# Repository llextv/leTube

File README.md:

# LeTube

**10 addressable LED tubes for stage lighting, controlled with Art-Net and QLC+.**

LeTube is a DIY project to build a set of 10 LED tubes for stage lighting.

The goal is pretty simple: build something similar to commercial pixel tubes, but for much less money and using hardware that I can actually modify and repair myself.

The tubes use WS2815 12V LED strips and are controlled by a single ESP32 running WLED. QLC+ sends the lighting data through Art-Net over Wi-Fi.

---

# Why am I doing this?

Commercial pixel tubes can get expensive very quickly when you need 10 of them.

I wanted to build my own version instead of buying ready-made tubes.

Another choice I made was to **not put an ESP32 inside every tube**. All the tubes are controlled from one ESP32, which keeps the electronics inside the tubes very simple.

The current version is mainly a prototype / personal project. I'm not trying to make a commercial product with it.

---

# Overview

## Features

* 10 × 1 m LED tubes
* WS2815 12V addressable RGB LEDs
* 144 LEDs/m
* One ESP32 for all 10 tubes
* Art-Net over Wi-Fi
* QLC+ compatible
* WLED based
* Centralized 12V power supply
* Power distribution using busbars
* Aluminium profiles with diffusers
* No controller inside the tubes

---

# Pictures

## 3D / Assembly

## WLED

---

# How it works
QLC+ generates the DMX values and sends them to the ESP32 using Art-Net.

The ESP32 receives the data and WLED handles the LED output.

Each tube contains a 1 meter section of WS2815 strip, so every LED can be controlled individually.

---

# LED Tubes

Each tube is made from an aluminium LED profile with a diffuser.

The current design uses:

* 1 m aluminium profile
* 1 m WS2815 strip
* 12V power
* LED diffuser
* Wiring for power and data

There is no microcontroller inside the tube.

The 10 tubes are connected back to the central controller and power distribution.

---

# Power

The whole LED system is powered from a **12V 600W power supply**.

I use two busbars to distribute the power.

The ESP32 is powered separately.

The reason for using centralized power is mostly simplicity. I don't need a power supply or converter inside every tube.

**The power supply can deliver a lot of current, so the final installation needs properly sized wiring and suitable protection/fusing.**

---

# Control

## WLED

The ESP32 runs WLED.

WLED is used to handle the addressable LEDs and the network communication.

Official documentation:

https://kno.wled.ge/

---

# Hardware

Main components:

* ESP32
* WS2815 12V LED strip
* Aluminium LED profiles
* LED diffusers
* 12V 600W power supply
* M6 power busbars
* Wiring and connectors

The complete BOM is available here:

[BOM.csv](BOM.csv)

---

# Project Files

## KiCad

The KiCad files are available here:

* [PCB](assets/tube.kicad_pcb)
* [Project](assets/tube.kicad_pro)
* [Schematic](assets/tube.kicad_sch)

## CAD

* [STEP model](cad/LeTube.step)

Usage of LeTube.step: this component is used for maintain the tube in horizontal position
---

# BOM

| Category           | Item                                        | Quantity | Unit Price (€) |    Total (€) | Notes                   |
| ------------------ | ------------------------------------------- | -------: | -------------: | -----------: | ----------------------- |
| Power Supply       | 12 V 600 W Switching Power Supply           |        1 |          35.99 |        35.99 | Main power supply       |
| Power Distribution | M6 Battery Bus Bar Power Distribution Block |        2 |           6.50 |        13.00 | 1 positive + 1 negative |
| LED Profile        | Aluminium LED Profile, 0.5 m                |       20 |           2.55 |        51.00 | 10 m total              |
| LED Strip          | WS2815 Addressable RGB LED Strip            |     10 m |          6.656 |        66.56 | 12 V                    |
| Wiring             | Electrical Wire                             |        — |           0.00 |         0.00 | Already available       |
| Controller         | ESP-WROOM-32                                |        1 |           0.00 |         0.00 | Already available       |
| **TOTAL**          |                                             |          |                | **176.55 €** | ≈ **195 USD**           |

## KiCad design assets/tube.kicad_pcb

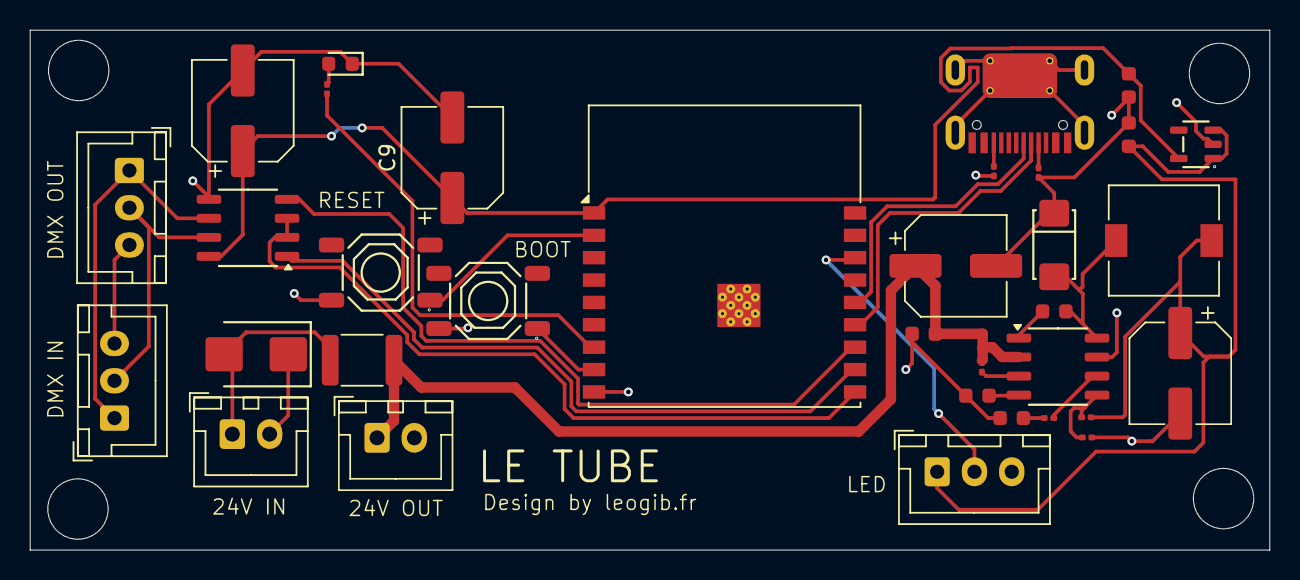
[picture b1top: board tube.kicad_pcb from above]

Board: 2 copper layers, 83.1 x 34.9 mm, 34 parts (0 on the bottom side), 26 nets.

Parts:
C1: 100 nF; C_0603
C2: 220 µF; CP_Elec_6.3x7.7
C3, C6, C9: 100 µF; CP_Elec_6.3x5.8
C4, C5: 10 nF; C_0603
C7, C8: 1uF; C_0603
C10: 100nF; C_0603
D1: SS34; D_DO-214AC(SMA)
D2: SMBJ33A; D_SMB
D3: LED; D_0603
F1: MF-MSMF200; Fuse_1812_4532Metric
J1: LED; JST_XH_B3B-XH-A_1x03_P2.50mm_Vertical
J2: 24V OUT; JST_XH_B2B-XH-A_1x02_P2.50mm_Vertical
J3: 24V IN; JST_XH_B2B-XH-A_1x02_P2.50mm_Vertical
J5: DMX OUT; JST_XH_B3B-XH-A_1x03_P2.50mm_Vertical
J6: USB_C_Receptacle_USB2.0_14P; TYPE-C-SMD_HX-TYPE-C-16PIN
J7: DMX IN; JST_XH_B3B-XH-A_1x03_P2.50mm_Vertical
L1: 22 µH 4 A; L_7.3x7.3_H4.5
R1: R100k; C_0201_0603Metric
R2, R4: R5.1k; C_0201_0603Metric
R3: R330; C_0201_0603Metric
R5: R105k; C_0201_0603Metric
R6: R20k; C_0201_0603Metric
R7: R10k; C_0201_0603Metric
SW2: RESET; SW-SMD_4P-L5.1-W5.1-P3.70-LS6.5-TL-2
SW3: Boot; SW-SMD_4P-L5.1-W5.1-P3.70-LS6.5-TL-2
U1: ESP32-C3-WROOM-02
U2: MAX3485; SOIC-8_3.9x4.9mm_P1.27mm
U3: TPS54331DR; SOIC-8_3.9x4.9mm_P1.27mm
U4: AP2112K-3.3; SOT-23-5_L3.0-W1.7-P0.95-LS2.8-BL

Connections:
3.3V: C6.1, C8.2, C9.1, U1.1 (3V3), U2.8 (VCC), U4.5 (VOUT)
+5V: C3.1, C7.1, J1.1, L1.2, R5.2, U4.1 (VIN), U4.3 (EN)
+24V: C2.1, C10.2, F1.1, J2.1, R1.1, U3.2 (VIN)
GNDREF: C2.2, C3.2, C4.2, C5.2, C6.2, C7.2, C8.1, C9.2, C10.1, D1.1 (K), D2.1 (A1), D3.1 (K), J1.3, J2.2, J3.2, J5.3, J7.3, R2.1, R4.1, R6.2, SW2.2, SW3.2, U1.9 (GND), U1.19 (GND), U2.5 (GND), U3.7 (GND), U4.2 (GND)
unnamed: C4.1, R7.2
unnamed: C1.2, D1.2 (A), L1.1, U3.8 (PH)
unnamed: D2.2 (A2), F1.2, J3.1
unnamed: D3.2 (A), R3.1
unnamed: J1.2, U1.16 (IO2)
unnamed: J5.1, J7.1, U2.6 (A)
unnamed: J5.2, J7.2, U2.7 (B)
unnamed: J6.A5 (CC1), R4.2
unnamed: J6.B5 (CC2), R2.2
unnamed: SW2.1, U1.2 (EN)
unnamed: R3.2, U1.7 (IO8)
unnamed: SW3.1, U1.8 (IO9)
unnamed: U1.10 (IO10), U2.2 (~RE), U2.3 (DE)
unnamed: J6.B7 (D-), U1.13 (IO18)
unnamed: J6.A6 (D+), U1.14 (IO19)
unnamed: U1.11 (IO20/RXD), U2.1 (RO)
unnamed: U1.12 (IO21/TXD), U2.4 (DI)
unnamed: C1.1, U3.1 (BOOT)
unnamed: R7.1, U3.6 (COMP)
unnamed: R1.2, U3.3 (EN)
unnamed: C5.1, U3.4 (SS)
unnamed: R5.1, R6.1, U3.5 (VSENSE)
